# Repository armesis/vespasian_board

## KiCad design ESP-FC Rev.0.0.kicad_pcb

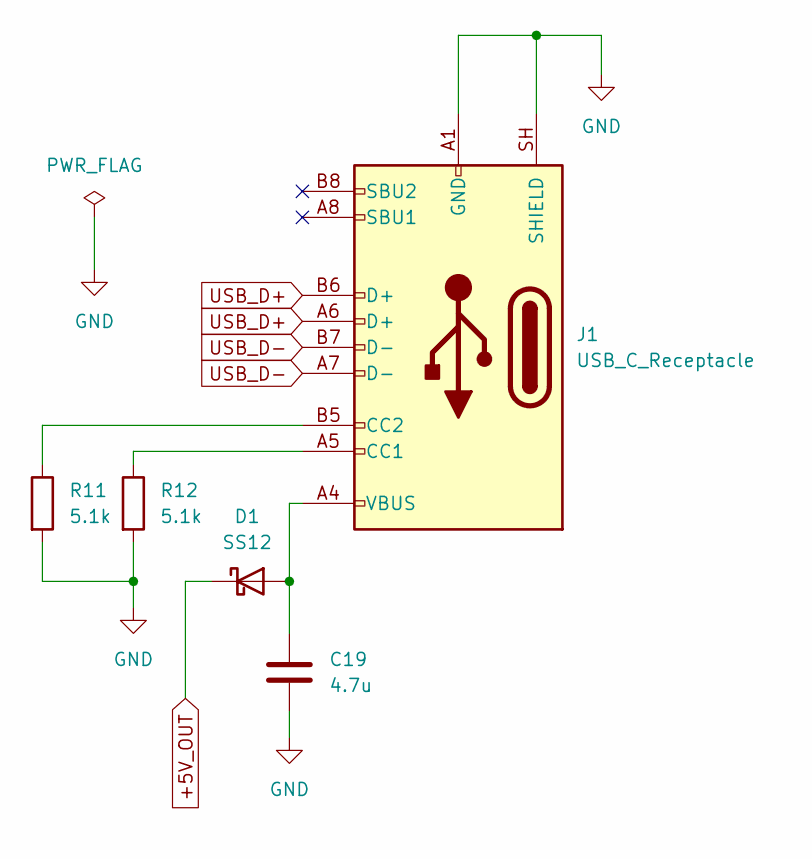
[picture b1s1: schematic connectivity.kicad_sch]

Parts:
C19: 4.7u; C_0805_2012Metric_Pad1.18x1.45mm_HandSolder
D1: SS12; D_SMA_Handsoldering
J1: USB_C_Receptacle; USB_C_Receptacle_XKB_U262-16XN-4BVC11
R11, R12: 5.1k; R_0603_1608Metric_Pad0.98x0.95mm_HandSolder

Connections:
+5V_OUT: D1.1 (K); also elsewhere on the board
GND: C19.2, J1.A1 (GND), J1.A12 (GND), J1.B1 (GND), J1.B12 (GND), J1.SH (SHIELD), R11.2, R12.2; also elsewhere on the board
unnamed: C19.1, D1.2 (A), J1.A4 (VBUS), J1.A9 (VBUS), J1.B4 (VBUS), J1.B9 (VBUS)
unnamed: J1.A5 (CC1), R12.1
unnamed: J1.B5 (CC2), R11.1
USB_D+: J1.A6 (D+), J1.B6 (D+); also elsewhere on the board
USB_D-: J1.A7 (D-), J1.B7 (D-); also elsewhere on the board

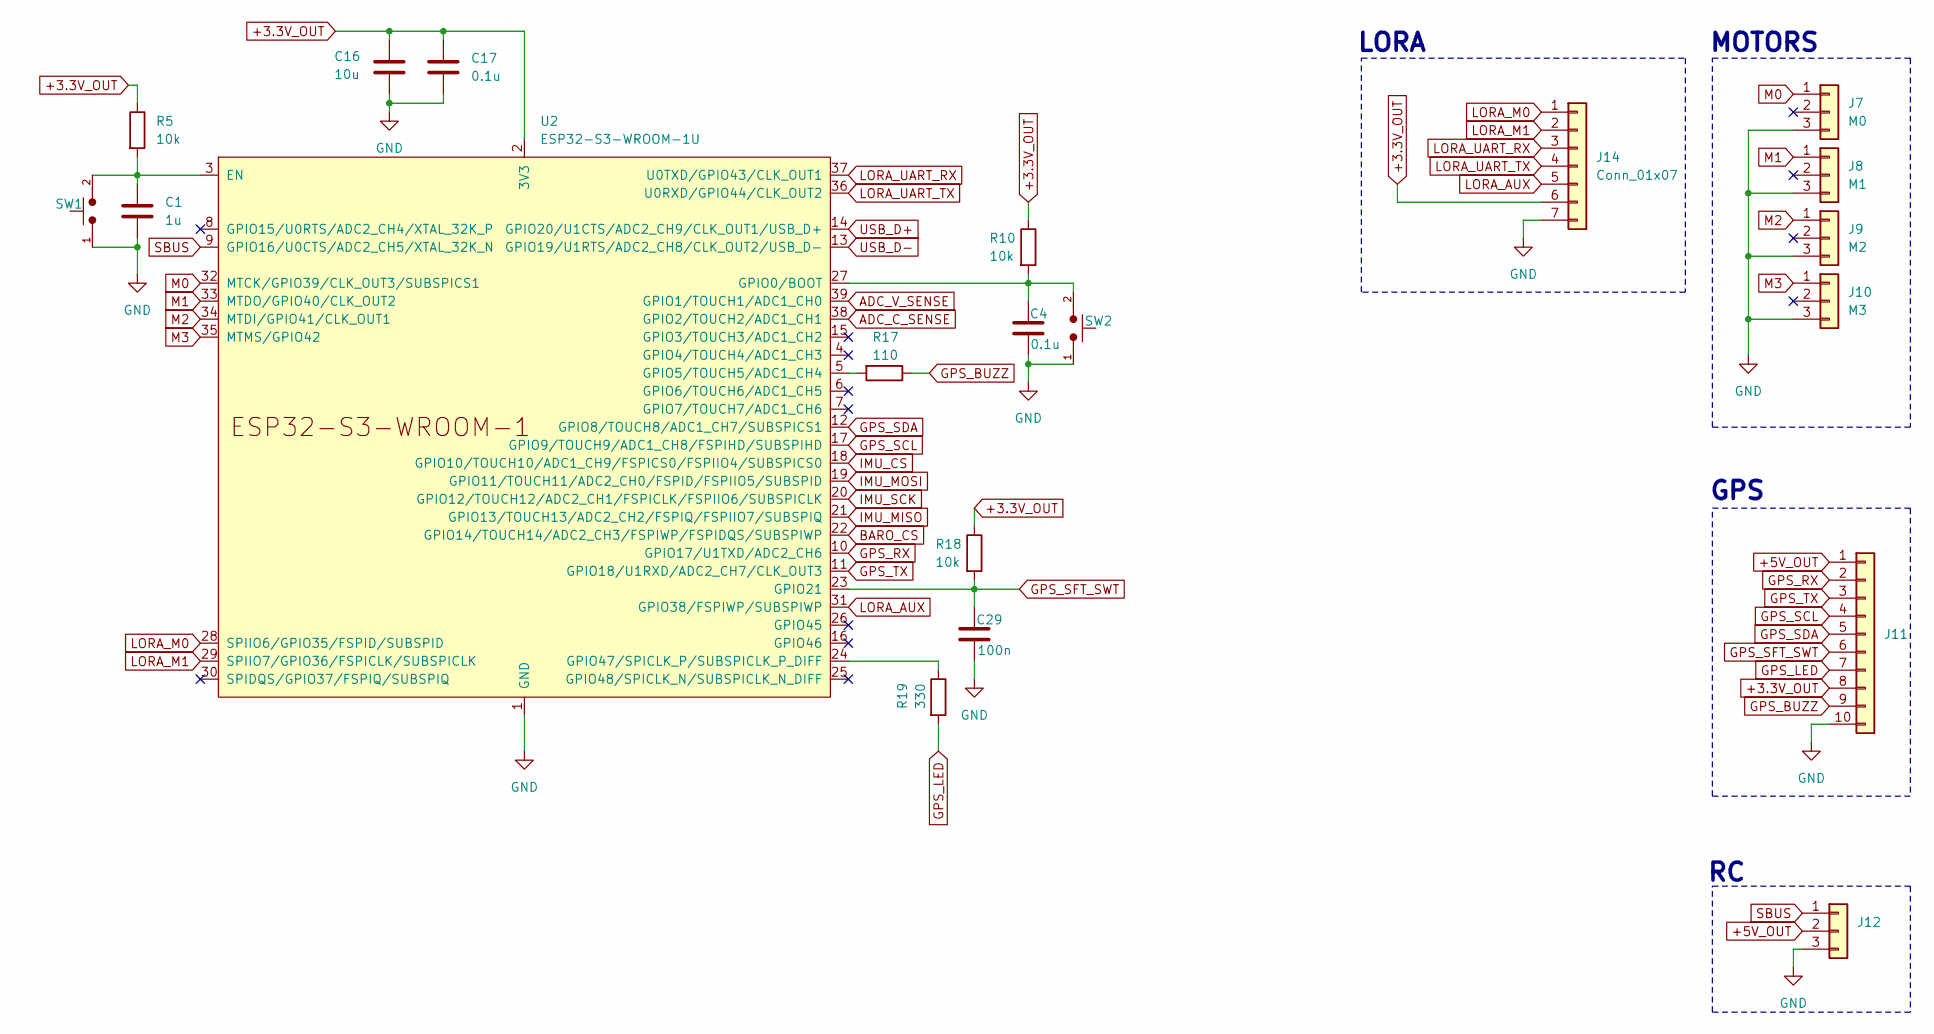
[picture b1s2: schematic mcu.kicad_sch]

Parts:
C1: 1u; C_0603_1608Metric_Pad1.08x0.95mm_HandSolder
C4, C17: 0.1u; C_0603_1608Metric_Pad1.08x0.95mm_HandSolder
C16: 10u; C_0805_2012Metric_Pad1.18x1.45mm_HandSolder
C29: 100n; C_0603_1608Metric_Pad1.08x0.95mm_HandSolder
J7: M0; PinHeader_1x03_P2.54mm_Horizontal
J8: M1; PinHeader_1x03_P2.54mm_Horizontal
J9: M2; PinHeader_1x03_P2.54mm_Horizontal
J10: M3; PinHeader_1x03_P2.54mm_Horizontal
J11: Conn_01x10; JST_GH_BM10B-GHS-TBT_1x10-1MP_P1.25mm_Vertical
J12: Conn_01x03; PinHeader_1x03_P2.54mm_Horizontal
J14: Conn_01x07; PinHeader_1x07_P2.54mm_Horizontal
R5, R10, R18: 10k; R_0603_1608Metric_Pad0.98x0.95mm_HandSolder
R17: 110; R_0603_1608Metric_Pad0.98x0.95mm_HandSolder
R19: 330; R_0603_1608Metric_Pad0.98x0.95mm_HandSolder
SW1, SW2: Push_Button; SW_PUSH_6mm
U2: ESP32-S3-WROOM-1U

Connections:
+3.3V_OUT: C16.1, C17.1, J11.8, J14.6, R5.1, R10.1, R18.1, U2.2 (3V3); also elsewhere on the board
+5V_OUT: J11.1, J12.2; also elsewhere on the board
ADC_C_SENSE: U2.38 (GPIO2/TOUCH2/ADC1_CH1); also elsewhere on the board
ADC_V_SENSE: U2.39 (GPIO1/TOUCH1/ADC1_CH0); also elsewhere on the board
BARO_CS: U2.22 (GPIO14/TOUCH14/ADC2_CH3/FSPIWP/FSPIDQS/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); also elsewhere on the board
GND: C1.2, C4.2, C16.2, C17.2, C29.2, J7.3, J8.3, J9.3, J10.3, J11.10, J12.3, J14.7, SW1.1, SW2.1, U2.1 (GND), U2.40 (GND), U2.41 (GND); also elsewhere on the board
GPS_BUZZ: J11.9, R17.1
GPS_LED: J11.7, R19.2
GPS_RX: J11.2, U2.10 (GPIO17/U1TXD/ADC2_CH6)
GPS_SCL: J11.4, U2.17 (GPIO9/TOUCH9/ADC1_CH8/FSPIHD/SUBSPIHD)
GPS_SDA: J11.5, U2.12 (GPIO8/TOUCH8/ADC1_CH7/SUBSPICS1)
GPS_SFT_SWT: C29.1, J11.6, R18.2, U2.23 (GPIO21)
GPS_TX: J11.3, U2.11 (GPIO18/U1RXD/ADC2_CH7/CLK_OUT3)
IMU_CS: U2.18 (GPIO10/TOUCH10/ADC1_CH9/FSPICS0/FSPIIO4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); also elsewhere on the board
IMU_MISO: U2.21 (GPIO13/TOUCH13/ADC2_CH2/FSPIQ/FSPIIO7/S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); also elsewhere on the board
IMU_MOSI: U2.19 (GPIO11/TOUCH11/ADC2_CH0/FSPID/FSPIIO5/S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); also elsewhere on the board
IMU_SCK: U2.20 (GPIO12/TOUCH12/ADC2_CH1/FSPICLK/FSPIIO6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); also elsewhere on the board
LORA_AUX: J14.5, U2.31 (GPIO38/FSPIWP/SUBSPIWP)
LORA_M0: J14.1, U2.28 (SPIIO6/GPIO35/FSPID/SUBSPID)
LORA_M1: J14.2, U2.29 (SPIIO7/GPIO36/FSPICLK/SUBSPICLK)
LORA_UART_RX: J14.3, U2.37 (U0TXD/GPIO43/CLK_OUT1)
LORA_UART_TX: J14.4, U2.36 (U0RXD/GPIO44/CLK_OUT2)
M0: J7.1, U2.32 (MTCK/GPIO39/CLK_OUT3/SUBSPICS1)
M1: J8.1, U2.33 (MTDO/GPIO40/CLK_OUT2)
M2: J9.1, U2.34 (MTDI/GPIO41/CLK_OUT1)
M3: J10.1, U2.35 (MTMS/GPIO42)
unnamed: C1.1, R5.2, SW1.2, U2.3 (EN)
unnamed: C4.1, R10.2, SW2.2, U2.27 (GPIO0/BOOT)
unnamed: R17.2, U2.5 (GPIO5/TOUCH5/ADC1_CH4)
unnamed: R19.1, U2.24 (GPIO47/SPICLK_P/SUBSPICLK_P_DIFF)
SBUS: J12.1, U2.9 (GPIO16/U0CTS/ADC2_CH5/XTAL_32K_N)
USB_D+: U2.14 (GPIO20/U1CTS/ADC2_CH9/CLK_OUT1/USB_D+); also elsewhere on the board
USB_D-: U2.13 (GPIO19/U1RTS/ADC2_CH8/CLK_OUT2/USB_D-); also elsewhere on the board

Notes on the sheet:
LORA
MOTORS
GPS

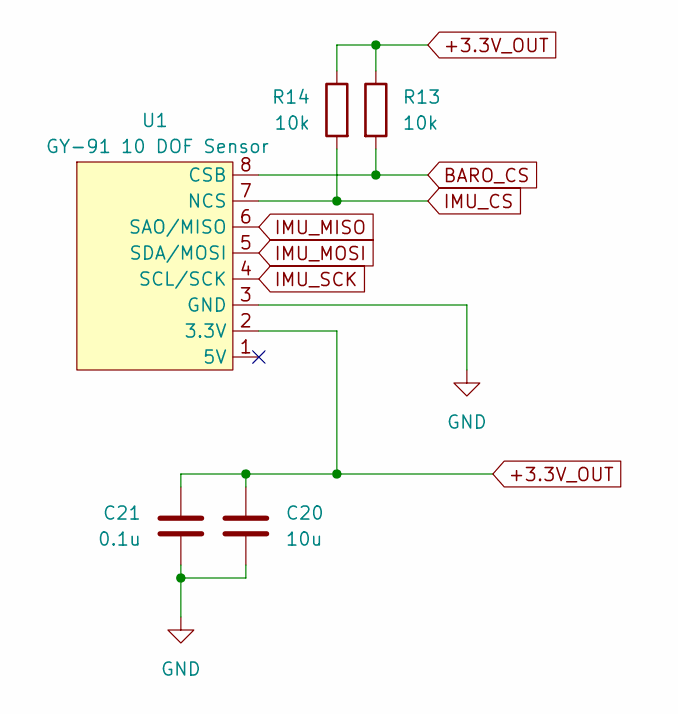
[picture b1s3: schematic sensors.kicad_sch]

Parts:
C20: 10u; C_0603_1608Metric_Pad1.08x0.95mm_HandSolder
C21: 0.1u; C_0603_1608Metric_Pad1.08x0.95mm_HandSolder
R13, R14: 10k; R_0603_1608Metric_Pad0.98x0.95mm_HandSolder
U1: GY-91 10 DOF Sensor; GY-91

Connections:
+3.3V_OUT: C20.1, C21.1, R13.1, R14.1, U1.2 (3.3V); also elsewhere on the board
BARO_CS: R13.2, U1.8 (CSB); also elsewhere on the board
GND: C20.2, C21.2, U1.3 (GND); also elsewhere on the board
IMU_CS: R14.2, U1.7 (NCS); also elsewhere on the board
IMU_MISO: U1.6 (SAO/MISO); also elsewhere on the board
IMU_MOSI: U1.5 (SDA/MOSI); also elsewhere on the board
IMU_SCK: U1.4 (SCL/SCK); also elsewhere on the board

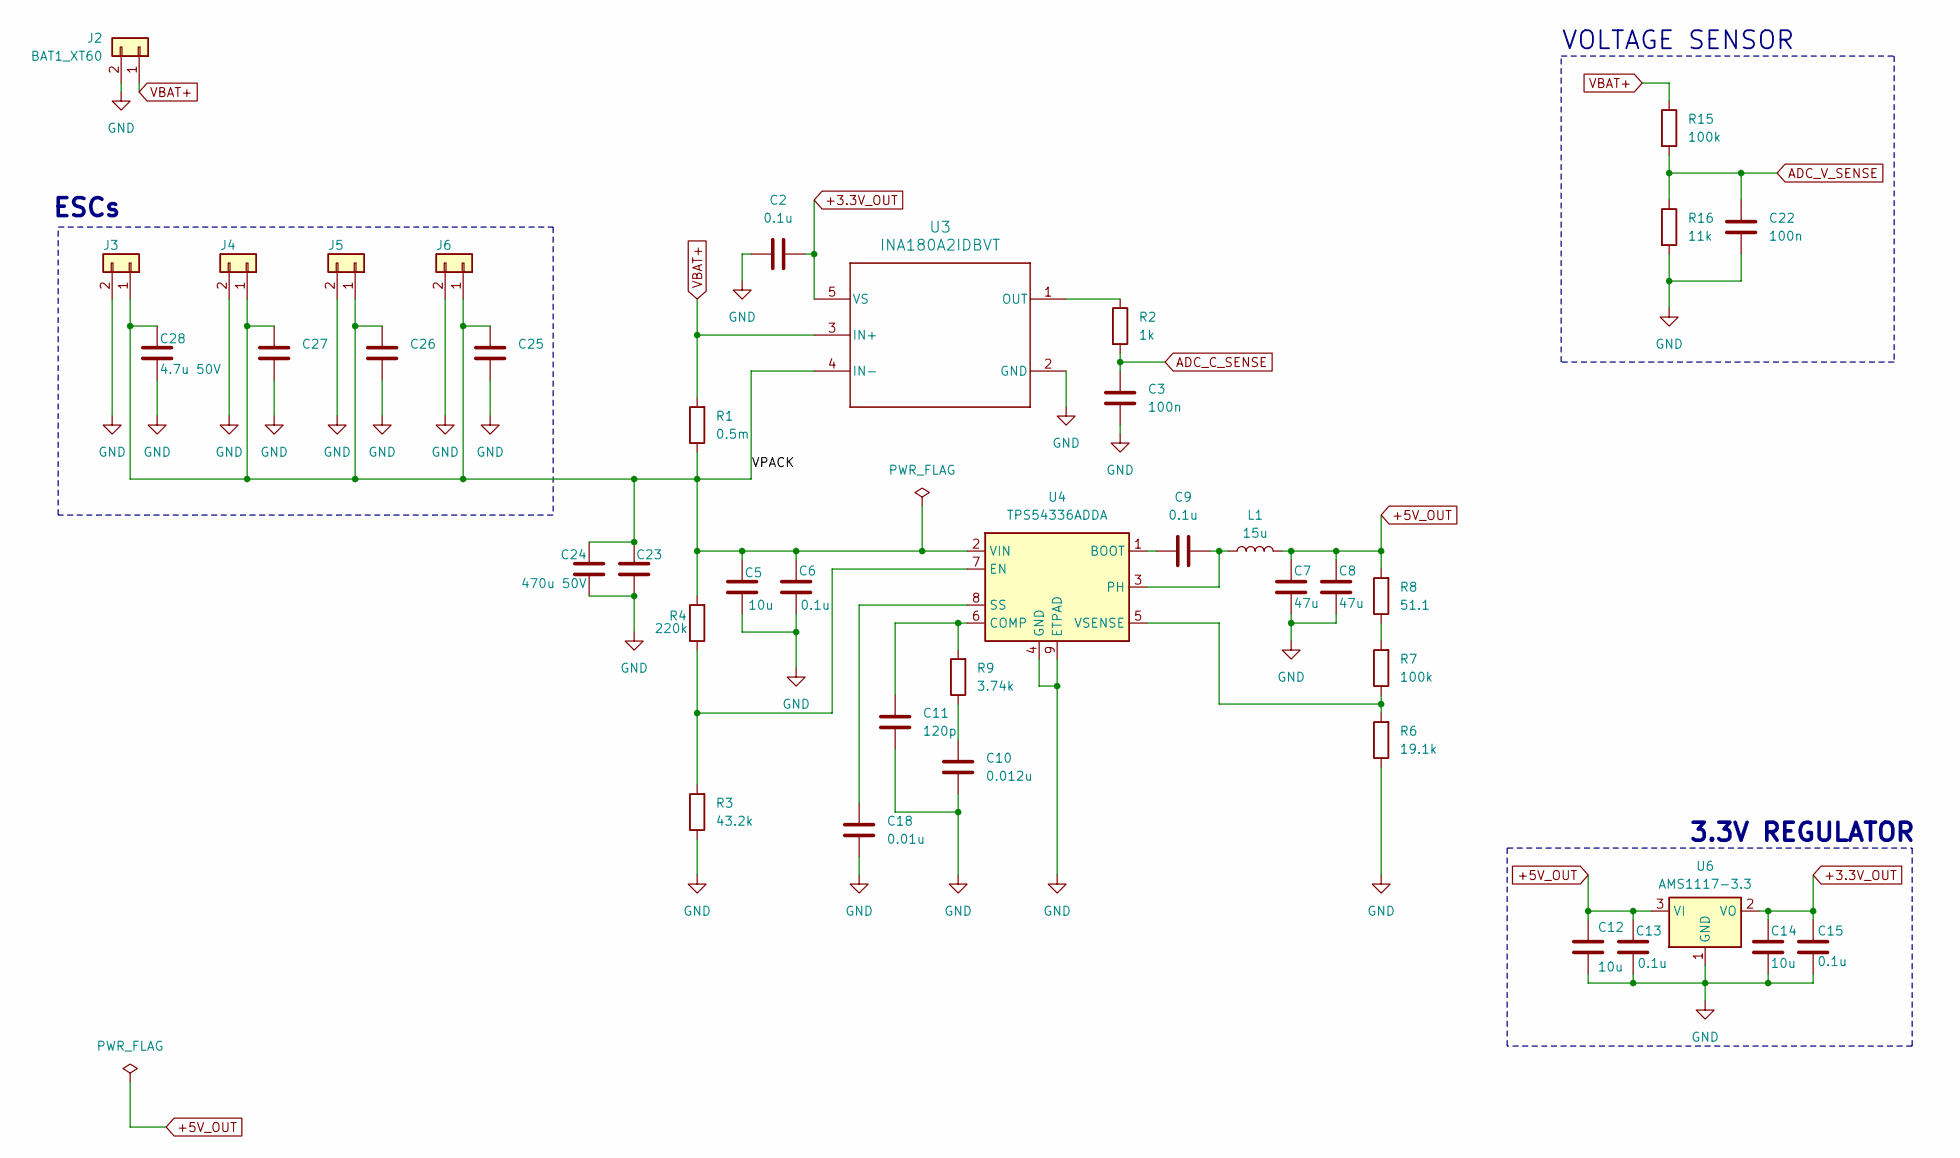
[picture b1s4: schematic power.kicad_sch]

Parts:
C2: 0.1u; C_0603_1608Metric
C3, C22: 100n; C_0603_1608Metric_Pad1.08x0.95mm_HandSolder
C5: 10u; C_1206_3216Metric_Pad1.33x1.80mm_HandSolder
C6, C9, C13, C15: 0.1u; C_0603_1608Metric_Pad1.08x0.95mm_HandSolder
C7, C8: 47u; C_1210_3225Metric_Pad1.33x2.70mm_HandSolder
C10: 0.012u; C_0603_1608Metric_Pad1.08x0.95mm_HandSolder
C11: 120p; C_0603_1608Metric_Pad1.08x0.95mm_HandSolder
C12, C14: 10u; C_0805_2012Metric_Pad1.18x1.45mm_HandSolder
C18: 0.01u; C_0603_1608Metric_Pad1.08x0.95mm_HandSolder
C23, C24: 470u 50V; CP_Radial_D10.0mm_P5.00mm
C25, C26, C27, C28: 4.7u 50V; C_1206_3216Metric_Pad1.33x1.80mm_HandSolder
J2: BAT1_XT60; AMASS_XT60PW-M_1x02_P7.20mm_Horizontal
J3, J4, J5, J6: Conn_01x02; AMASS_XT30PW-F_1x02_P2.50mm_Horizontal
L1: 15u; L_APV_APH0630
R1: 0.5m; RES_L500x_BRN
R2: 1k; R_0805_2012Metric
R3: 43.2k; R_0603_1608Metric_Pad0.98x0.95mm_HandSolder
R4: 220k; R_0603_1608Metric_Pad0.98x0.95mm_HandSolder
R6: 19.1k; R_0603_1608Metric_Pad0.98x0.95mm_HandSolder
R7, R15: 100k; R_0603_1608Metric_Pad0.98x0.95mm_HandSolder
R8: 51.1; R_0603_1608Metric_Pad0.98x0.95mm_HandSolder
R9: 3.74k; R_0603_1608Metric_Pad0.98x0.95mm_HandSolder
R16: 11k; R_0603_1608Metric_Pad0.98x0.95mm_HandSolder
U3: INA180A2IDBVT; DBV0005A_N
U4: TPS54336ADDA; TI_SO-PowerPAD-8_ThermalVias
U6: AMS1117-3.3; SOT-223-3_TabPin2

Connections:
+3.3V_OUT: C2.2, C14.1, C15.1, U3.5 (VS), U6.2 (VO); also elsewhere on the board
+5V_OUT: C7.1, C8.1, C12.1, C13.1, L1.2, R8.2, U6.3 (VI); also elsewhere on the board
/Power/VPACK: C5.1, C6.1, C23.2, C24.2, C25.2, C26.2, C27.2, C28.2, J3.1, J4.1, J5.1, J6.1, R1.1, R4.2, U3.4 (IN-), U4.2 (VIN)
ADC_C_SENSE: C3.1, R2.2; also elsewhere on the board
ADC_V_SENSE: C22.1, R15.2, R16.1; also elsewhere on the board
GND: C2.1, C3.2, C5.2, C6.2, C7.2, C8.2, C10.2, C11.2, C12.2, C13.2, C14.2, C15.2, C18.2, C22.2, C23.1, C24.1, C25.1, C26.1, C27.1, C28.1, J2.2, J3.2, J4.2, J5.2, J6.2, R3.1, R6.1, R16.2, U3.2 (GND), U4.4 (GND), U4.9 (ETPAD), U6.1 (GND); also elsewhere on the board
unnamed: C10.1, R9.1
unnamed: R7.2, R8.1
unnamed: R2.1, U3.1 (OUT)
unnamed: C9.1, U4.1 (BOOT)
unnamed: C11.1, R9.2, U4.6 (COMP)
unnamed: R3.2, R4.1, U4.7 (EN)
unnamed: C9.2, L1.1, U4.3 (PH)
unnamed: C18.1, U4.8 (SS)
unnamed: R6.2, R7.1, U4.5 (VSENSE)
VBAT+: J2.1, R1.2, R15.1, U3.3 (IN+)

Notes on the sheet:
VOLTAGE SENSOR
ESCs
3.3V REGULATOR

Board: 2 copper layers, 70 parts (0 on the bottom side), 47 nets, no tracks yet.
